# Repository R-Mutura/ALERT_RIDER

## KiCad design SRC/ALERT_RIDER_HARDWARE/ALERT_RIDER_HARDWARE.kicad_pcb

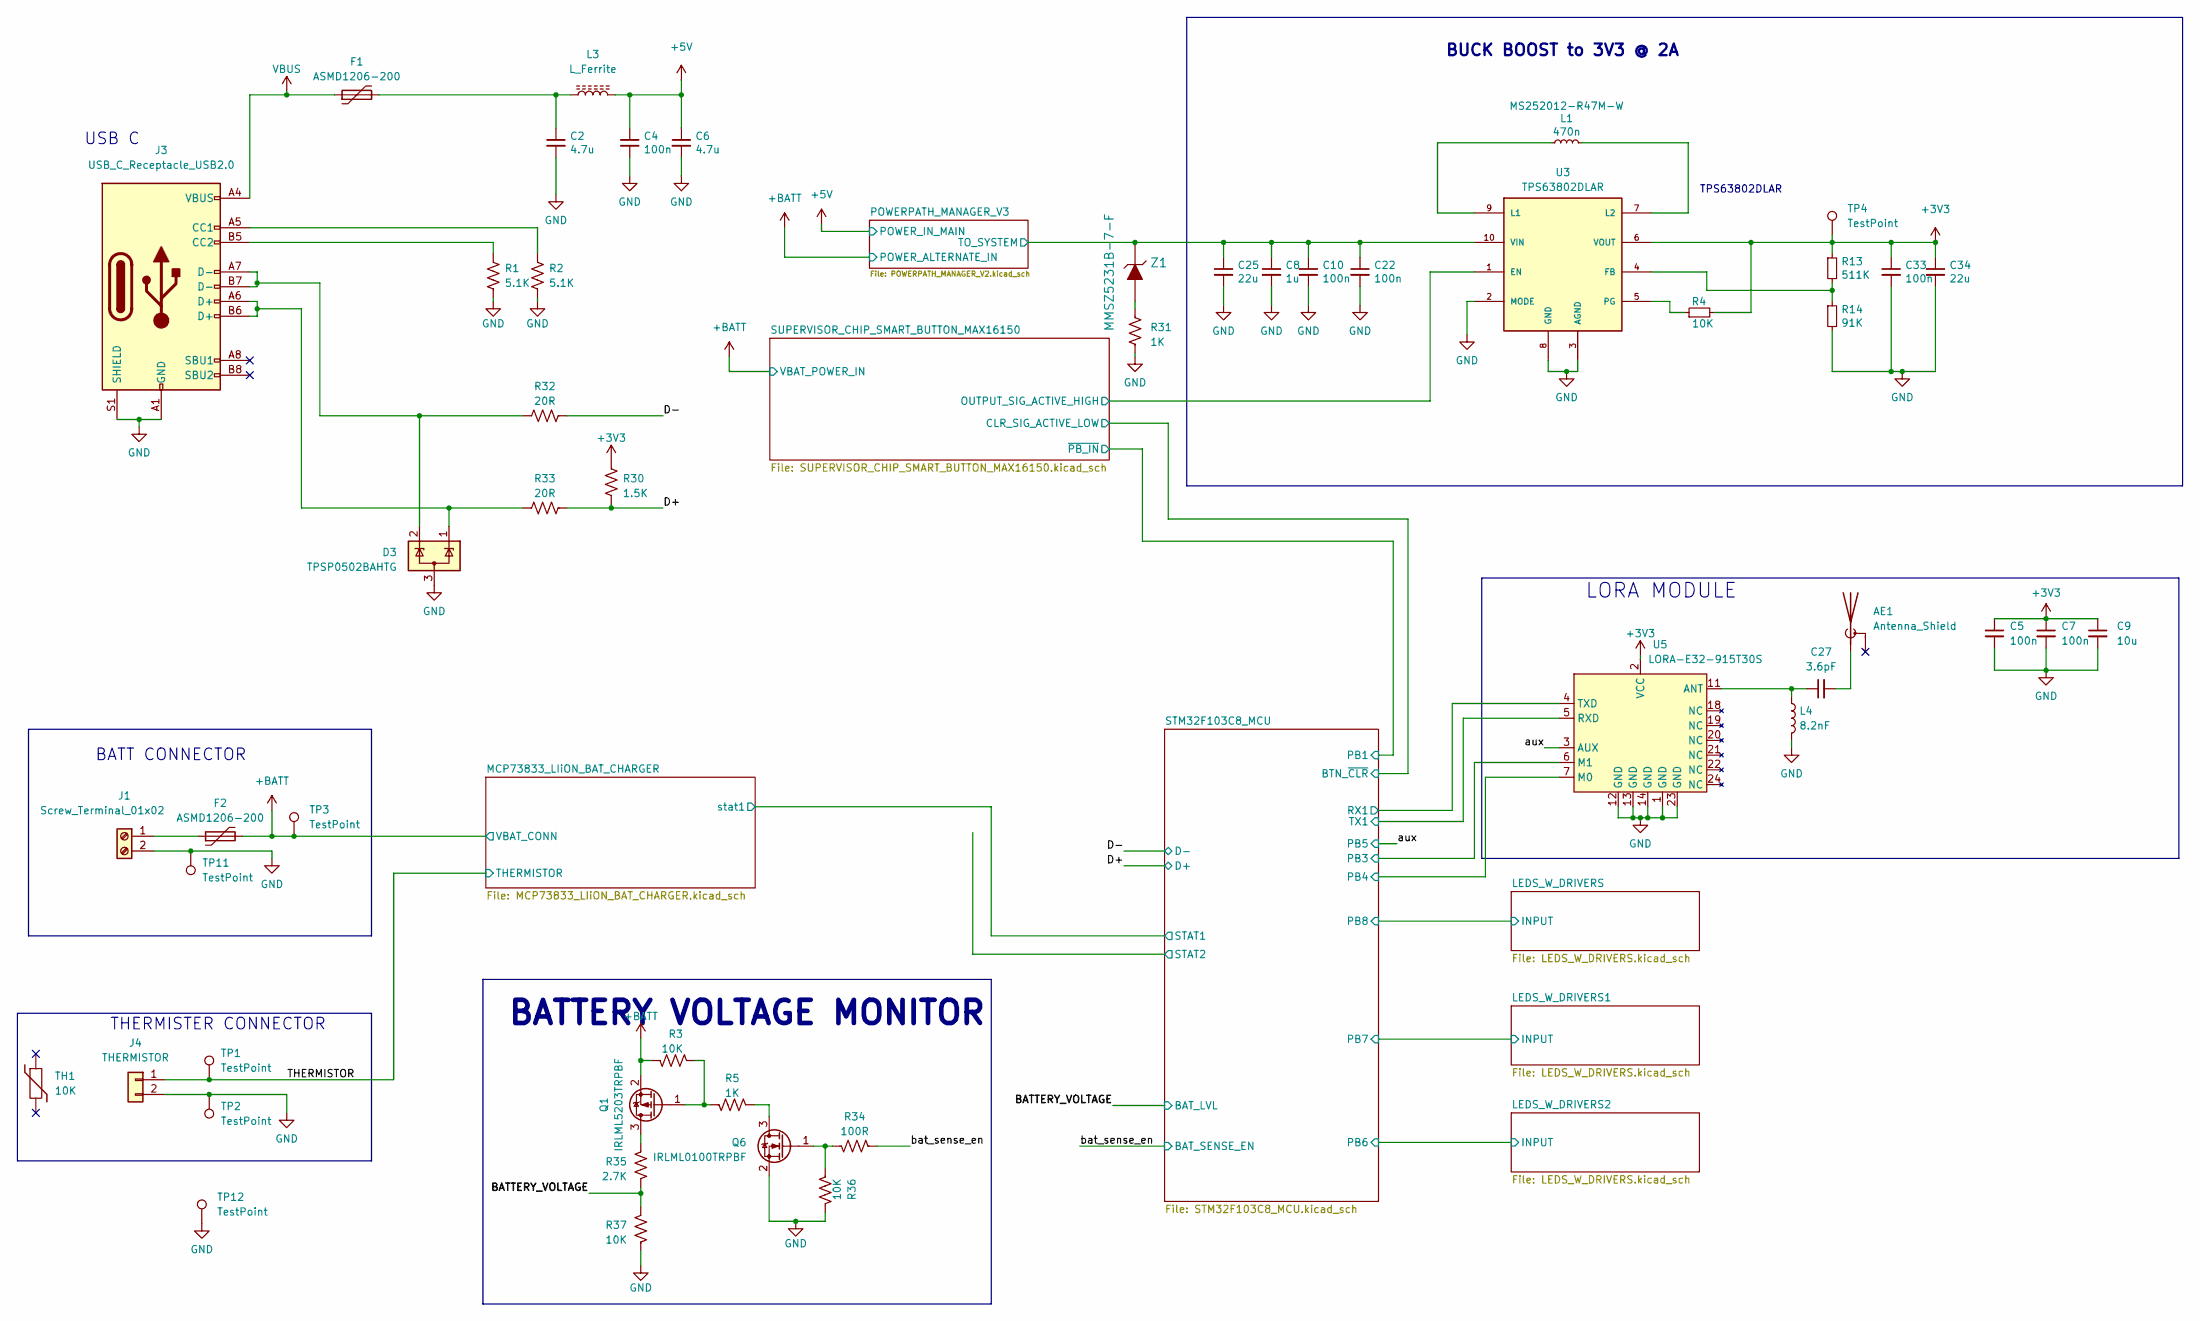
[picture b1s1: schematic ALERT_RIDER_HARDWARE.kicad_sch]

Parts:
AE1: Antenna_Shield; antenna-W3136
C2, C6: 4.7u; C_0603_1608Metric
C4, C10: 100n; C_0603_1608Metric
C5, C7, C22, C33: 100n; C_0402_1005Metric
C8: 1u; C_0603_1608Metric
C9: 10u; C_0402_1005Metric
C25, C34: 22u; C_0603_1608Metric
C27: 3.6pF; C_0402_1005Metric
D3: TPSP0502BAHTG; SOT-23
F1, F2: ASMD1206-200; Fuse_1206_3216Metric
J1: Screw_Terminal_01x02; JST_XH_S2B-XH-A_1x02_P2.50mm_Horizontal
J3: USB_C_Receptacle_USB2.0; MC-311D_USB_C_2.0_12PIN
J4: THERMISTOR; JST_EH_B2B-EH-A_1x02_P2.50mm_Vertical
L1: 470n; L_1008_2520Metric; MPN MS252012-R47M-W
L3: L_Ferrite; L_0603_1608Metric
L4: 8.2nF; L_0402_1005Metric
Q1: IRLML5203TRPBF; SOT-23
Q6: IRLML0100TRPBF; SOT-23
R1, R2: 5.1K; R_0402_1005Metric
R3, R36, R37: 10K; R_0402_1005Metric
R4: 10K; R_0603_1608Metric
R5, R31: 1K; R_0402_1005Metric
R13: 511K; R_0603_1608Metric
R14: 91K; R_0603_1608Metric
R30: 1.5K; R_0402_1005Metric
R32, R33: 20R; R_0402_1005Metric
R34: 100R; R_0402_1005Metric
R35: 2.7K; R_0402_1005Metric
TH1: 10K
TP1, TP2, TP3, TP4, TP11, TP12: TestPoint; TestPoint_Pad_D0.9mm
U3: TPS63802DLAR; VREG_TPS63802DLAR; PARTREV B
U5: LORA-E32-915T30S; LORA-E32-915T30S-SMD
Z1: MMSZ5231B-7-F; SOD-123; MPN MMSZ5231B-7-F; Digi-Key_PN MMSZ5231B-FDICT-ND

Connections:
+3V3: C5.1, C7.1, C9.1, C33.1, C34.1, R4.2, R13.1, R30.1, TP4.1, U3.6 (VOUT), U5.2 (VCC); also elsewhere on the board
+5V: C4.1, C6.1, L3.2; also elsewhere on the board
+BATT: F2.2, Q1.2 (S), R3.1, TP3.1; also elsewhere on the board
/BATTERY_VOLTAGE: R35.2, R37.1; also elsewhere on the board
/D+: R30.2, R33.2; also elsewhere on the board
/D-: R32.2; also elsewhere on the board
/POWERPATH_MANAGER_V3/TO_SYSTEM: C8.1, C10.1, C22.1, C25.1, U3.10 (VIN), Z1.K; also elsewhere on the board
/STM32F103C8_MCU/PB3: U5.6 (M1); also elsewhere on the board
/STM32F103C8_MCU/PB4: U5.7 (M0); also elsewhere on the board
/STM32F103C8_MCU/RX1: U5.4 (TXD); also elsewhere on the board
/STM32F103C8_MCU/TX1: U5.5 (RXD); also elsewhere on the board
/SUPERVISOR_CHIP_SMART_BUTTON_MAX16150/OUTPUT_SIG_ACTIVE_HIGH: U3.1 (EN); also elsewhere on the board
/THERMISTOR: J4.1, TP1.1; also elsewhere on the board
/aux: U5.3 (AUX); also elsewhere on the board
/bat_sense_en: R34.2; also elsewhere on the board
GND: C2.2, C4.2, C5.2, C6.2, C7.2, C8.2, C9.2, C10.2, C22.2, C25.2, C33.2, C34.2, D3.3 (A), J1.2, J3.A1 (GND), J3.A12 (GND), J3.B1 (GND), J3.B12 (GND), J3.S1 (SHIELD), J4.2, L4.2, Q6.2 (S), R1.2, R2.2, R14.2, R31.2, R36.2, R37.2, TP2.1, TP11.1, TP12.1, U3.2 (MODE), U3.3 (AGND), U3.8 (GND), U5.1 (GND), U5.12 (GND), U5.13 (GND), U5.14 (GND), U5.23 (GND); also elsewhere on the board
unnamed: AE1.1 (A), C27.2
unnamed: C2.1, F1.2, L3.1
unnamed: D3.1 (K), J3.A6 (D+), J3.B6 (D+), R33.1
unnamed: D3.2 (K), J3.A7 (D-), J3.B7 (D-), R32.1
unnamed: F2.1, J1.1
unnamed: J3.A5 (CC1), R2.1
unnamed: J3.B5 (CC2), R1.1
unnamed: Q1.3 (D), R35.1
unnamed: Q1.1 (G), R3.2, R5.1
unnamed: Q6.3 (D), R5.2
unnamed: Q6.1 (G), R34.1, R36.1
unnamed: R31.1, Z1.A
unnamed: R13.2, R14.1, U3.4 (FB)
unnamed: L1.1, U3.9 (L1)
unnamed: L1.2, U3.7 (L2)
unnamed: R4.1, U3.5 (PG)
unnamed: C27.1, L4.1, U5.11 (ANT)
VBUS: F1.1, J3.A4 (VBUS), J3.A9 (VBUS), J3.B4 (VBUS), J3.B9 (VBUS)

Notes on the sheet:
BUCK BOOST to 3V3 @ 2A
LORA MODULE
BATT CONNECTOR
USB C
BATTERY VOLTAGE MONITOR
TPS63802DLAR
THERMISTER CONNECTOR

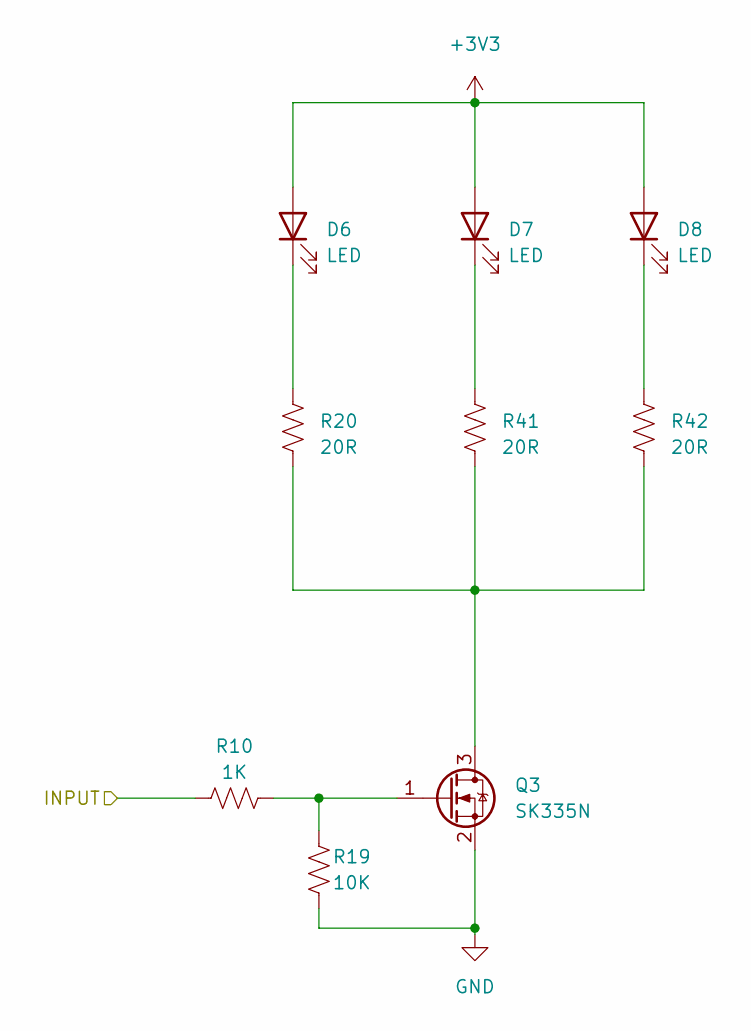
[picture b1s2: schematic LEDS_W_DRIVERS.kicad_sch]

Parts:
D6, D7, D8: LED; LED_PLCC_2835_Handsoldering
Q3: SK335N; SOT-23
R10: 1K; R_0402_1005Metric
R19: 10K; R_0402_1005Metric
R20, R41, R42: 20R; R_0402_1005Metric

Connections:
+3V3: D6.2 (A), D7.2 (A), D8.2 (A); also elsewhere on the board
/LEDS_W_DRIVERS/INPUT: R10.1; also elsewhere on the board
GND: Q3.2 (S), R19.1; also elsewhere on the board
unnamed: D6.1 (K), R20.1
unnamed: D7.1 (K), R41.1
unnamed: D8.1 (K), R42.1
unnamed: Q3.3 (D), R20.2, R41.2, R42.2
unnamed: Q3.1 (G), R10.2, R19.2

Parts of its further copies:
D9, D10, D11, D12, D13, D14: LED; LED_PLCC_2835_Handsoldering
Q4, Q5: SK335N; SOT-23
R21, R24: 1K; R_0402_1005Metric
R22, R25: 10K; R_0402_1005Metric
R23, R26, R43, R44, R45, R46: 20R; R_0402_1005Metric

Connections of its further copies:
+3V3: D9.2 (A), D10.2 (A), D11.2 (A), D12.2 (A), D13.2 (A), D14.2 (A); also elsewhere on the board
/LEDS_W_DRIVERS1/INPUT: R21.1; also elsewhere on the board
/LEDS_W_DRIVERS2/INPUT: R24.1; also elsewhere on the board
GND: Q4.2 (S), Q5.2 (S), R22.1, R25.1; also elsewhere on the board
unnamed: D9.1 (K), R23.1
unnamed: D10.1 (K), R43.1
unnamed: D11.1 (K), R44.1
unnamed: D12.1 (K), R26.1
unnamed: D13.1 (K), R45.1
unnamed: D14.1 (K), R46.1
unnamed: Q4.3 (D), R23.2, R43.2, R44.2
unnamed: Q4.1 (G), R21.2, R22.2
unnamed: Q5.3 (D), R26.2, R45.2, R46.2
unnamed: Q5.1 (G), R24.2, R25.2

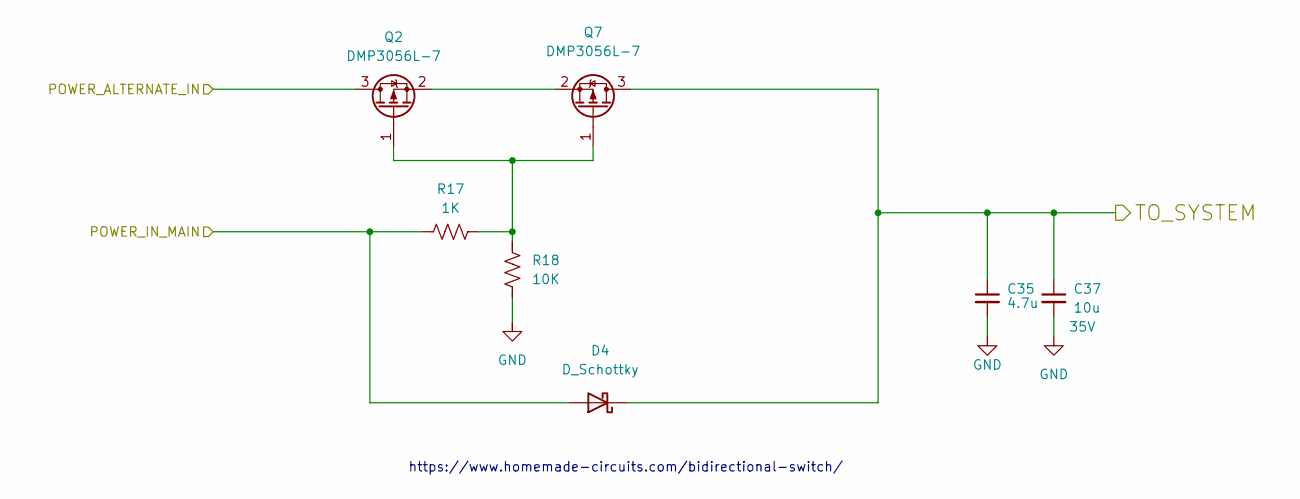
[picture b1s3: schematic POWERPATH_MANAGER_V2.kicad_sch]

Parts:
C35: 4.7u; C_0603_1608Metric
C37: 10u; C_0603_1608Metric; VOLTAGE 35V
D4: D_Schottky; D_SMA
Q2, Q7: DMP3056L-7; SOT-23
R17: 1K; R_0603_1608Metric
R18: 10K; R_0603_1608Metric

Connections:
+5V: D4.2 (A), R17.1; also elsewhere on the board
+BATT: Q2.3 (D); also elsewhere on the board
/POWERPATH_MANAGER_V3/TO_SYSTEM: C35.1, C37.1, D4.1 (K), Q7.3 (D); also elsewhere on the board
GND: C35.2, C37.2, R18.2; also elsewhere on the board
unnamed: Q2.1 (G), Q7.1 (G), R17.2, R18.1
unnamed: Q2.2 (S), Q7.2 (S)

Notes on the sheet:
https://www.homemade-circuits.com/bidirectional-switch/

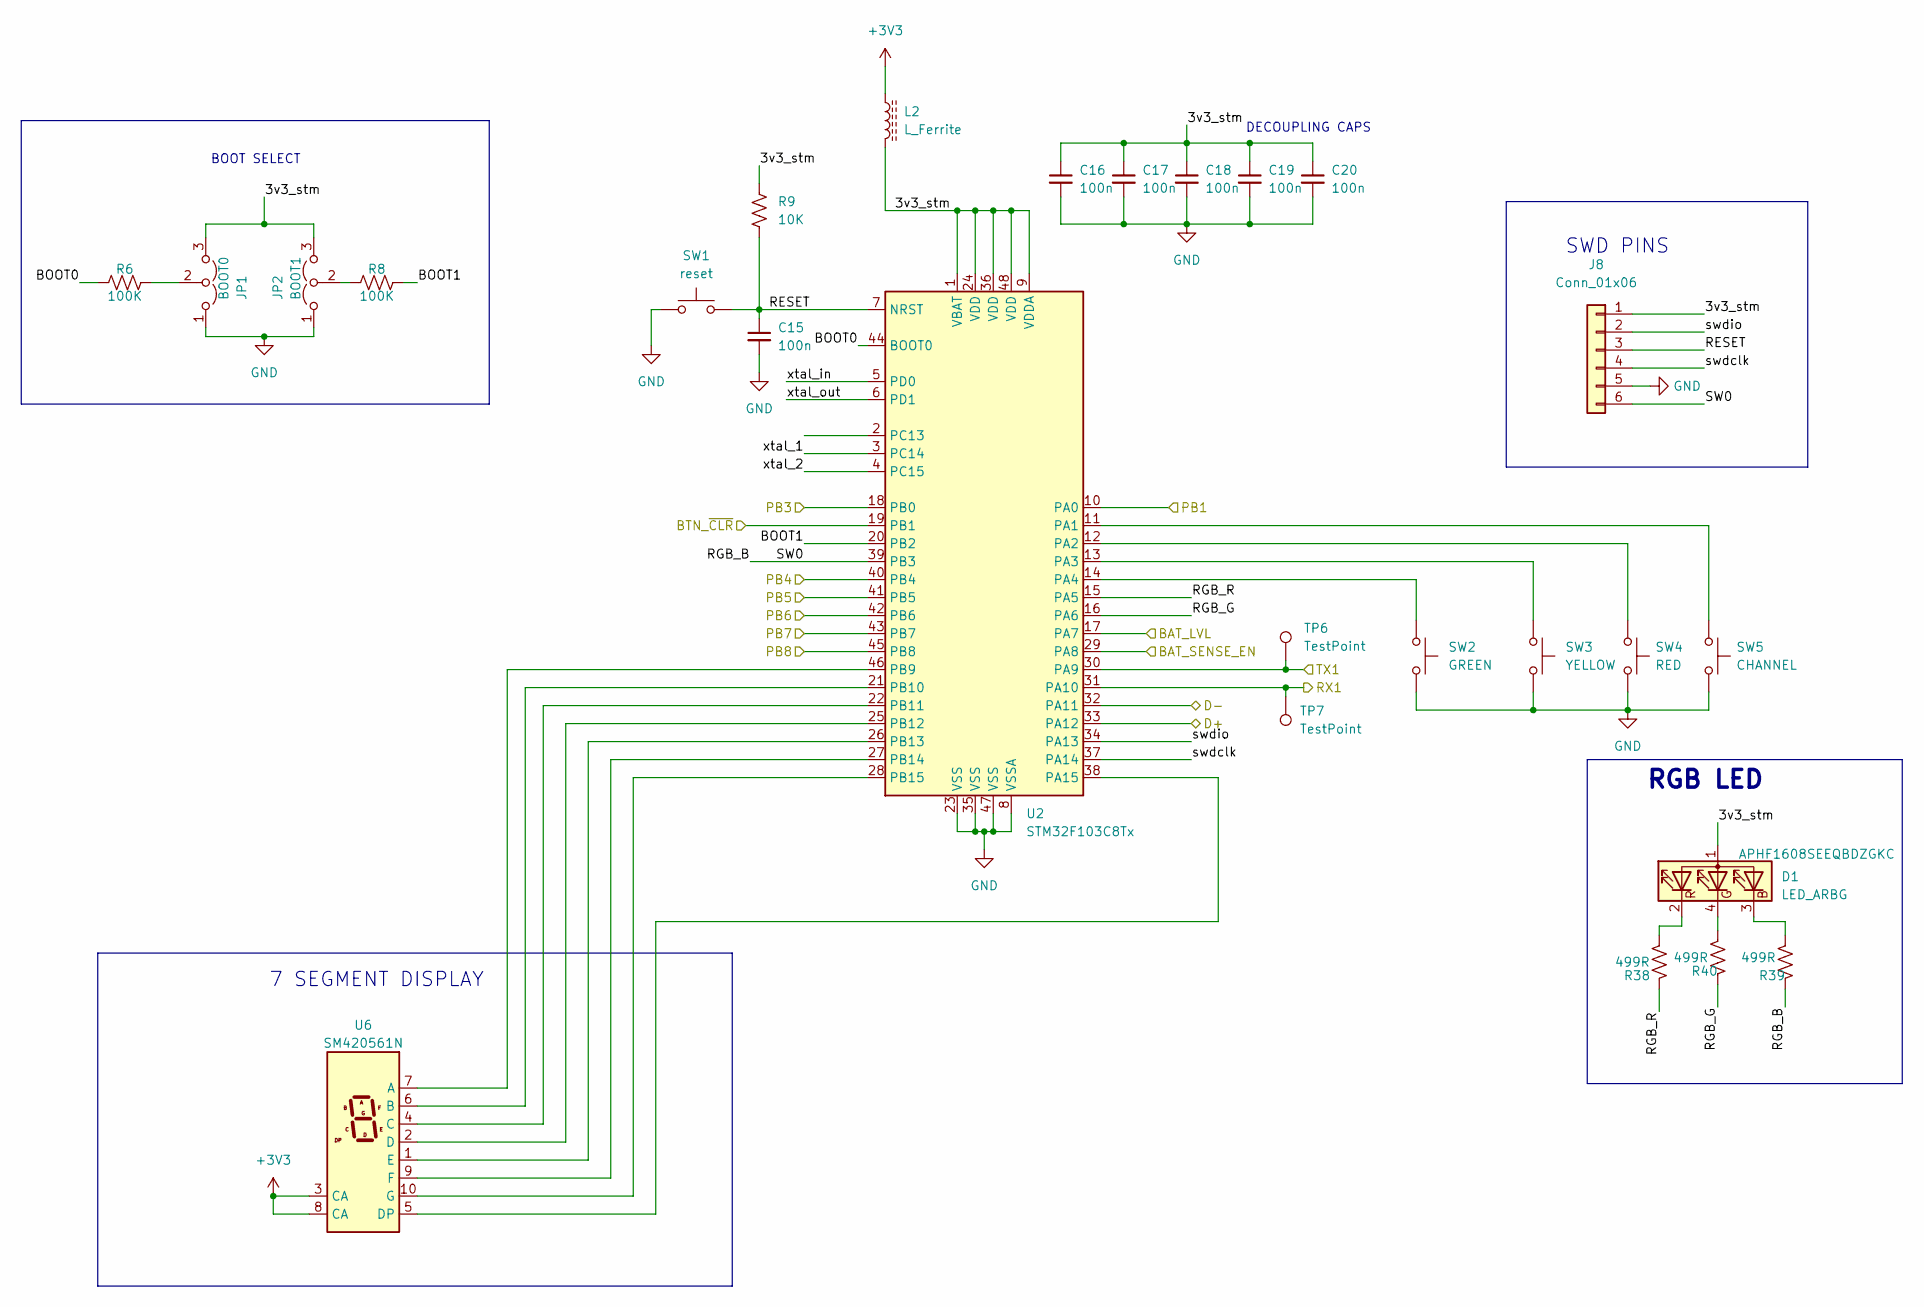
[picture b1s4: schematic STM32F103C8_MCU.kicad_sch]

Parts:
C15, C16, C17, C18, C19, C20: 100n; C_0402_1005Metric
D1: LED_ARBG; LED_APHF1608SEEQBDZGKC; MPN APHF1608SEEQBDZGKC
J8: Conn_01x06; J-LINK_6-PIN_NEEDLE_ADAPTER
JP1: BOOT0; SolderJumper-3_P1.3mm_Open_RoundedPad1.0x1.5mm_NumberLabels
JP2: BOOT1; SolderJumper-3_P1.3mm_Open_RoundedPad1.0x1.5mm_NumberLabels
L2: L_Ferrite; L_0603_1608Metric
R6, R8: 100K; R_0402_1005Metric
R9: 10K; R_0402_1005Metric
R38, R39, R40: 499R; R_0402_1005Metric
SW1: reset; SKRPACE010
SW2: GREEN; SW_SPST_EVQQ2; MPN EVQQ2K03W
SW3: YELLOW; SW_SPST_EVQQ2; MPN EVQQ2K03W
SW4: RED; SW_SPST_EVQQ2; MPN EVQQ2K03W
SW5: CHANNEL; SW_SPST_EVQQ2; MPN EVQQ2K03W
TP6, TP7: TestPoint; TestPoint_Pad_D0.9mm
U2: STM32F103C8Tx; LQFP-48_7x7mm_P0.5mm
U6: SM420561N; SEGMENT-SLS0281FR1A1GD

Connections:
+3V3: L2.1, U6.3 (CA), U6.8 (CA); also elsewhere on the board
/BATTERY_VOLTAGE: U2.17 (PA7); also elsewhere on the board
/D+: U2.33 (PA12); also elsewhere on the board
/D-: U2.32 (PA11); also elsewhere on the board
/LEDS_W_DRIVERS1/INPUT: U2.43 (PB7); also elsewhere on the board
/LEDS_W_DRIVERS2/INPUT: U2.42 (PB6); also elsewhere on the board
/LEDS_W_DRIVERS/INPUT: U2.45 (PB8); also elsewhere on the board
/STM32F103C8_MCU/3v3_stm: C16.1, C17.1, C18.1, C19.1, C20.1, D1.1 (A), J8.1, JP1.3 (B), JP2.3 (B), L2.2, R9.1, U2.1 (VBAT), U2.9 (VDDA), U2.24 (VDD), U2.36 (VDD), U2.48 (VDD)
/STM32F103C8_MCU/BOOT0: R6.1, U2.44 (BOOT0)
/STM32F103C8_MCU/BOOT1: R8.2, U2.20 (PB2)
/STM32F103C8_MCU/BTN_~CLR: U2.19 (PB1); also elsewhere on the board
/STM32F103C8_MCU/PB1: U2.10 (PA0); also elsewhere on the board
/STM32F103C8_MCU/PB3: U2.18 (PB0); also elsewhere on the board
/STM32F103C8_MCU/PB4: U2.40 (PB4); also elsewhere on the board
/STM32F103C8_MCU/RESET: C15.1, J8.3, R9.2, SW1.2, U2.7 (NRST)
/STM32F103C8_MCU/RGB_B: J8.6, R39.1, U2.39 (PB3)
/STM32F103C8_MCU/RGB_G: R40.1, U2.16 (PA6)
/STM32F103C8_MCU/RGB_R: R38.1, U2.15 (PA5)
/STM32F103C8_MCU/RX1: TP7.1, U2.31 (PA10); also elsewhere on the board
/STM32F103C8_MCU/TX1: TP6.1, U2.30 (PA9); also elsewhere on the board
/STM32F103C8_MCU/swdclk: J8.4, U2.37 (PA14)
/STM32F103C8_MCU/swdio: J8.2, U2.34 (PA13)
/STM32F103C8_MCU/xtal_1: U2.3 (PC14)
/STM32F103C8_MCU/xtal_2: U2.4 (PC15)
/STM32F103C8_MCU/xtal_in: U2.5 (PD0)
/STM32F103C8_MCU/xtal_out: U2.6 (PD1)
/aux: U2.41 (PB5); also elsewhere on the board
/bat_sense_en: U2.29 (PA8); also elsewhere on the board
GND: C15.2, C16.2, C17.2, C18.2, C19.2, C20.2, J8.5, JP1.1 (A), JP2.1 (A), SW1.1, SW2.1, SW3.1, SW4.1, SW5.1, U2.8 (VSSA), U2.23 (VSS), U2.35 (VSS), U2.47 (VSS); also elsewhere on the board
unnamed: D1.3 (BK), R39.2
unnamed: D1.4 (GK), R40.2
unnamed: D1.2 (RK), R38.2
unnamed: JP1.2 (C), R6.2
unnamed: JP2.2 (C), R8.1
unnamed: SW5.2, U2.11 (PA1)
unnamed: SW4.2, U2.12 (PA2)
unnamed: SW3.2, U2.13 (PA3)
unnamed: SW2.2, U2.14 (PA4)
unnamed: U2.38 (PA15), U6.5 (DP)
unnamed: U2.46 (PB9), U6.7 (A)
unnamed: U2.21 (PB10), U6.6 (B)
unnamed: U2.22 (PB11), U6.4 (C)
unnamed: U2.25 (PB12), U6.2 (D)
unnamed: U2.26 (PB13), U6.1 (E)
unnamed: U2.27 (PB14), U6.9 (F)
unnamed: U2.28 (PB15), U6.10 (G)

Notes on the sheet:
7 SEGMENT DISPLAY
DECOUPLING CAPS
SWD PINS
RGB LED
BOOT SELECT

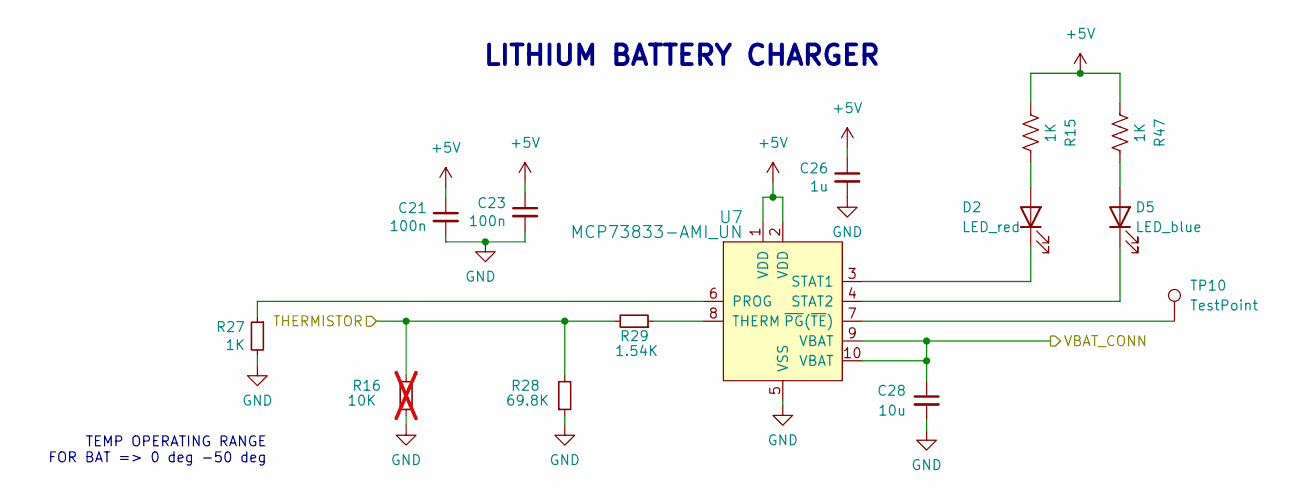
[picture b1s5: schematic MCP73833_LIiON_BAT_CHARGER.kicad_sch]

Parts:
C21, C23: 100n; C_0402_1005Metric
C26: 1u; C_0603_1608Metric
C28: 10u; C_0603_1608Metric
D2: LED_red; LED_0402_1005Metric
D5: LED_blue; LED_0402_1005Metric
R15, R27, R47: 1K; R_0402_1005Metric
R16: 10K; R_0402_1005Metric; not fitted
R28: 69.8K; R_0402_1005Metric
R29: 1.54K; R_0402_1005Metric
TP10: TestPoint; TestPoint_Pad_D0.9mm
U7: MCP73833-AMI_UN; MSOP-10_W3mm; MPN MCP73833-AMI/UN; Digi-Key_PN MCP73833-AMI/UN-ND

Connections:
+5V: C21.1, C23.1, C26.1, R15.1, R47.1, U7.1 (VDD), U7.2 (VDD); also elsewhere on the board
+BATT: C28.1, U7.9 (VBAT), U7.10 (VBAT); also elsewhere on the board
/THERMISTOR: R16.2, R28.2, R29.2; also elsewhere on the board
GND: C21.2, C23.2, C26.2, C28.2, R16.1, R27.2, R28.1, U7.5 (VSS); also elsewhere on the board
unnamed: D2.2 (A), R15.2
unnamed: D2.1 (K), U7.3 (STAT1)
unnamed: D5.2 (A), R47.2
unnamed: D5.1 (K), U7.4 (STAT2)
unnamed: R27.1, U7.6 (PROG)
unnamed: R29.1, U7.8 (THERM)
unnamed: TP10.1, U7.7 (~PG(~TE))

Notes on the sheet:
TEMP OPERATING RANGE FOR BAT => 0 deg -50 deg
LITHIUM BATTERY CHARGER

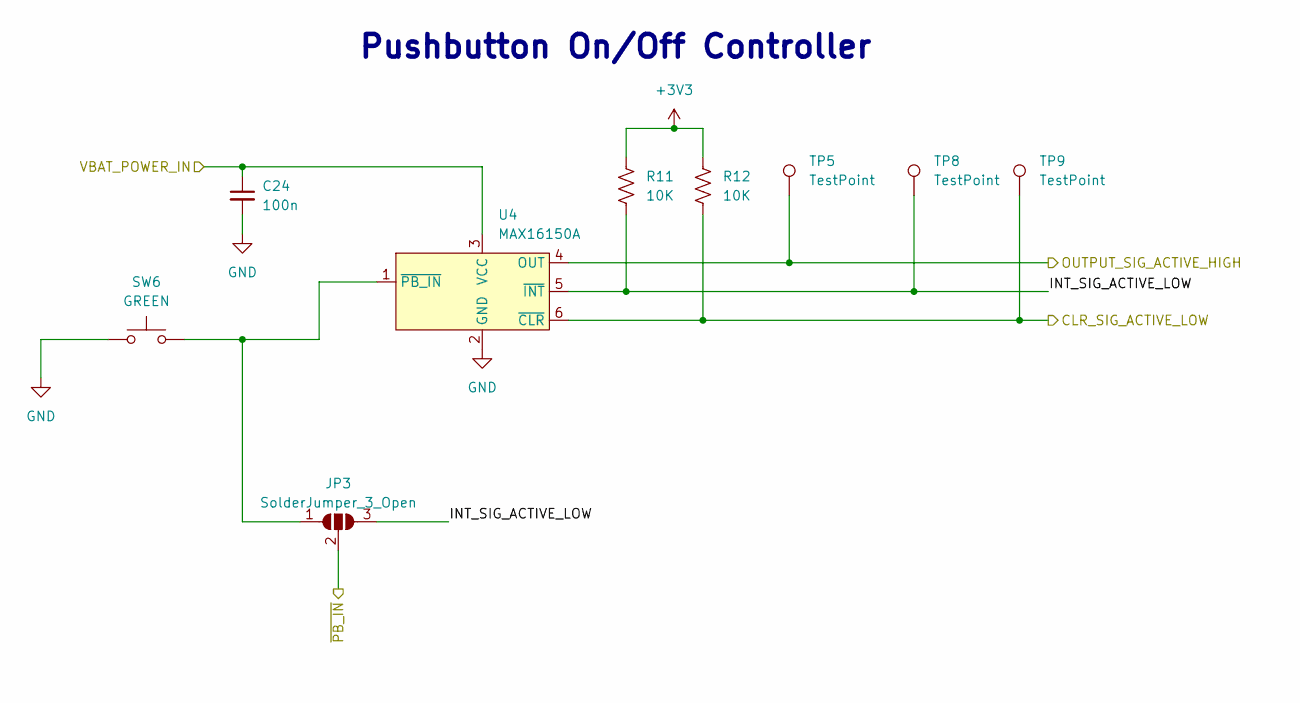
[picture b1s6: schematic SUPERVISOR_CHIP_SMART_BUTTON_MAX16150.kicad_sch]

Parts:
C24: 100n; C_0402_1005Metric
JP3: SolderJumper_3_Open; SolderJumper-3_P1.3mm_Open_RoundedPad1.0x1.5mm_NumberLabels
R11, R12: 10K; R_0402_1005Metric
SW6: GREEN; SW_SPST_EVQQ2; MPN EVQQ2K03W
TP5, TP8, TP9: TestPoint; TestPoint_Pad_D0.9mm
U4: MAX16150A; SOT-23-6

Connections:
+3V3: R11.1, R12.1; also elsewhere on the board
+BATT: C24.1, U4.3 (VCC); also elsewhere on the board
/STM32F103C8_MCU/BTN_~CLR: R12.2, TP9.1, U4.6 (~CLR); also elsewhere on the board
/STM32F103C8_MCU/PB1: JP3.2 (C); also elsewhere on the board
/SUPERVISOR_CHIP_SMART_BUTTON_MAX16150/INT_SIG_ACTIVE_LOW: JP3.3 (B), R11.2, TP8.1, U4.5 (~INT)
/SUPERVISOR_CHIP_SMART_BUTTON_MAX16150/OUTPUT_SIG_ACTIVE_HIGH: TP5.1, U4.4 (OUT); also elsewhere on the board
GND: C24.2, SW6.2, U4.2 (GND); also elsewhere on the board
unnamed: JP3.1 (A), SW6.1, U4.1 (~PB_IN)

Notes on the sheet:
Pushbutton On/Off Controller

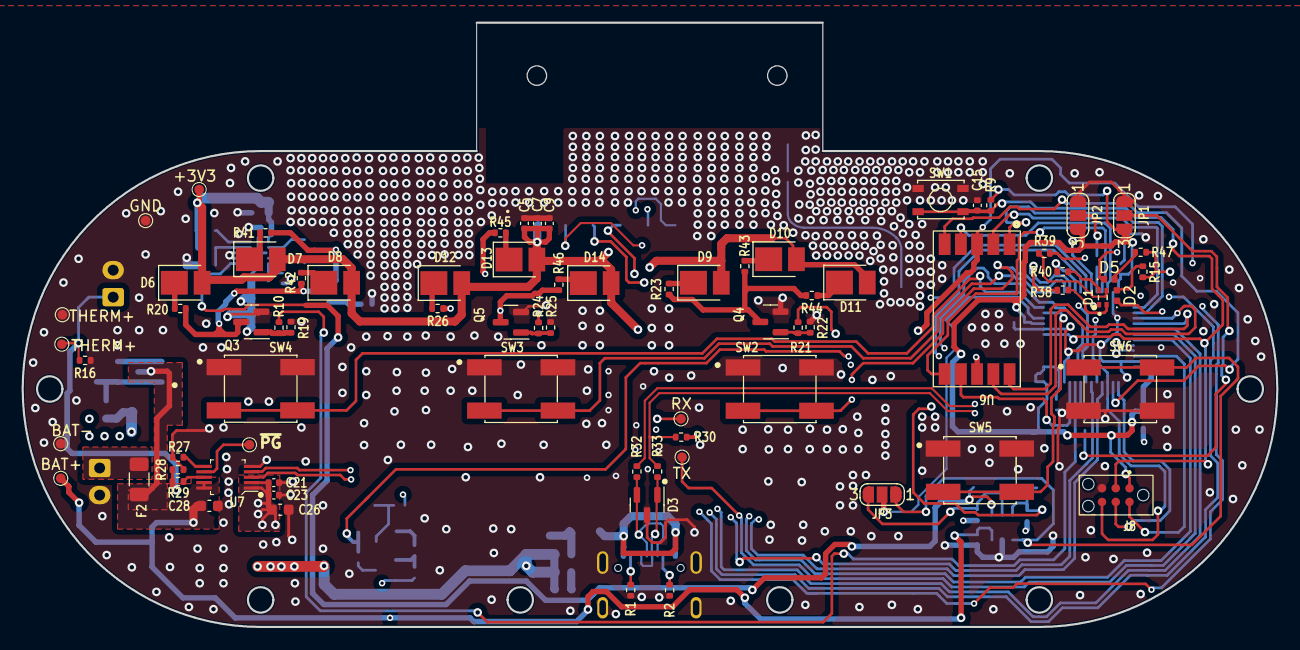
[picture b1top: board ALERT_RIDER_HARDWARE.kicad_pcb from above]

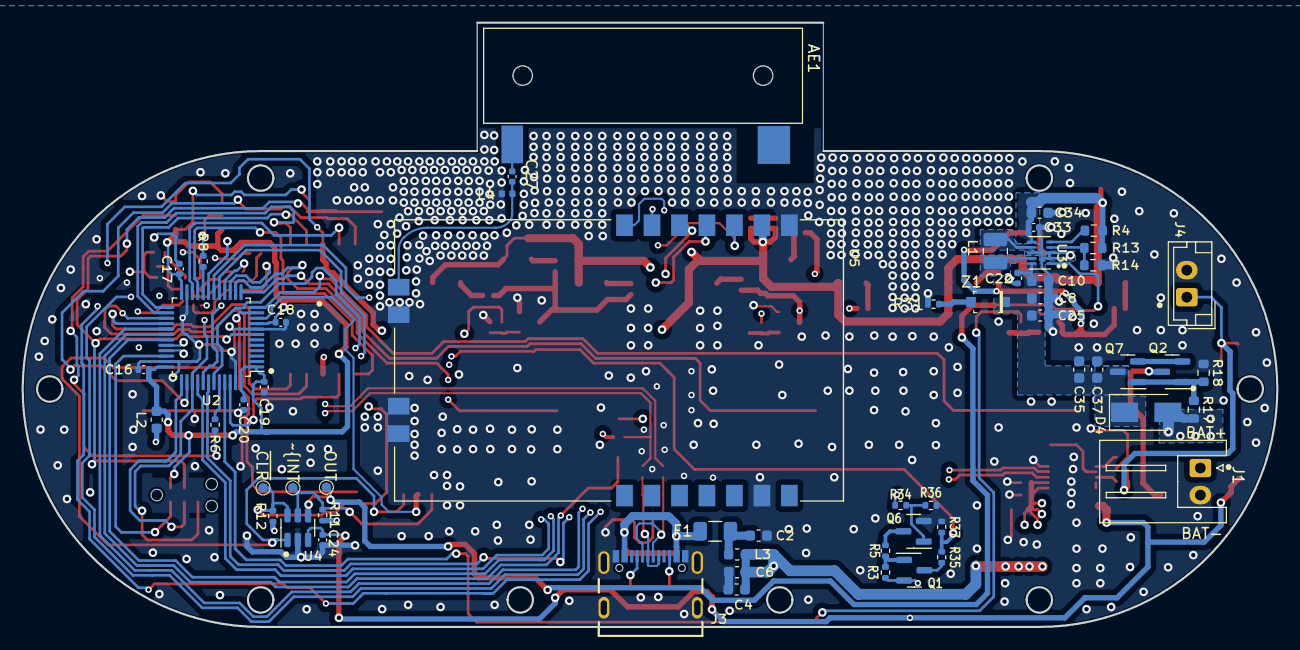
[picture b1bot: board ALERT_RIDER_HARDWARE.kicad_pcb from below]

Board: 4 copper layers, 116.0 x 55.9 mm, 132 parts (56 on the bottom side), 91 nets.

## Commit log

2023-12-03 complete routing and layout
2023-12-04 complete Pa8-Pa7 LED placement maximized all files generated
2023-12-14 complete update on production files and Design files
2023-12-24 alert rider updated complete internal rc HSI version
2023-12-24 led update gerber placmenet
2023-12-29 confirmation of BOM
